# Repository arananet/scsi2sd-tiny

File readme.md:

# SCSI2SD

SCSI2SD is an open project made by Michael McMaster that replace your old SCSI drive device with a SCSI emulator using micro-sd.

# SCSI-TINY

I made this new tiny design from the original SCSI2SD schematics using EAGLE PCB Software. This particular design contains two SD sockets, one for micro-sd and one for SD. This is a working and tested design by many users. They are on sale in AmigaStore and also a batch has been made in 2018 for the RETROWIKI forum.

# Updates

25/10/2019: Initial release. HW made in 2018.

# License

SCSI2SD copyright (c) Michael McMaster | http://www.codesrc.com/mediawiki/index.php?title=SCSI2SD

SCSI2SD-Tiny copyright (c) 2018 Eduardo Arana | @edu_arana

This project is released under the GNU v3 license. You can redistribute it and/or modify it under the terms of the GNU General Public License as published by the Free Software Foundation, either version 3 of the License, or (at your option) any later version.

This program is distributed in the hope that it will be useful, but WITHOUT ANY WARRANTY.

See the GNU General Public License for more details.

There is a copy of the GPLv3 license in this repository. If not, see http://www.gnu.org/licenses/.

## The source/designs of any modifications must be provided to those you distribute the board to.

# Feedback

If you find any error on this description, please drop me an email to info@arananet.net or # Feedback

If you find any error on this description, please drop me an email to info@arananet.net or If you like the project or want to support it, you can buy me a beer or a KO-FI :)

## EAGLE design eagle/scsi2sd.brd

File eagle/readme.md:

If you are gonna produce a batch of this board remember to quote the original authors, don't be a pcb lammer, leave the original authors on the PCB.

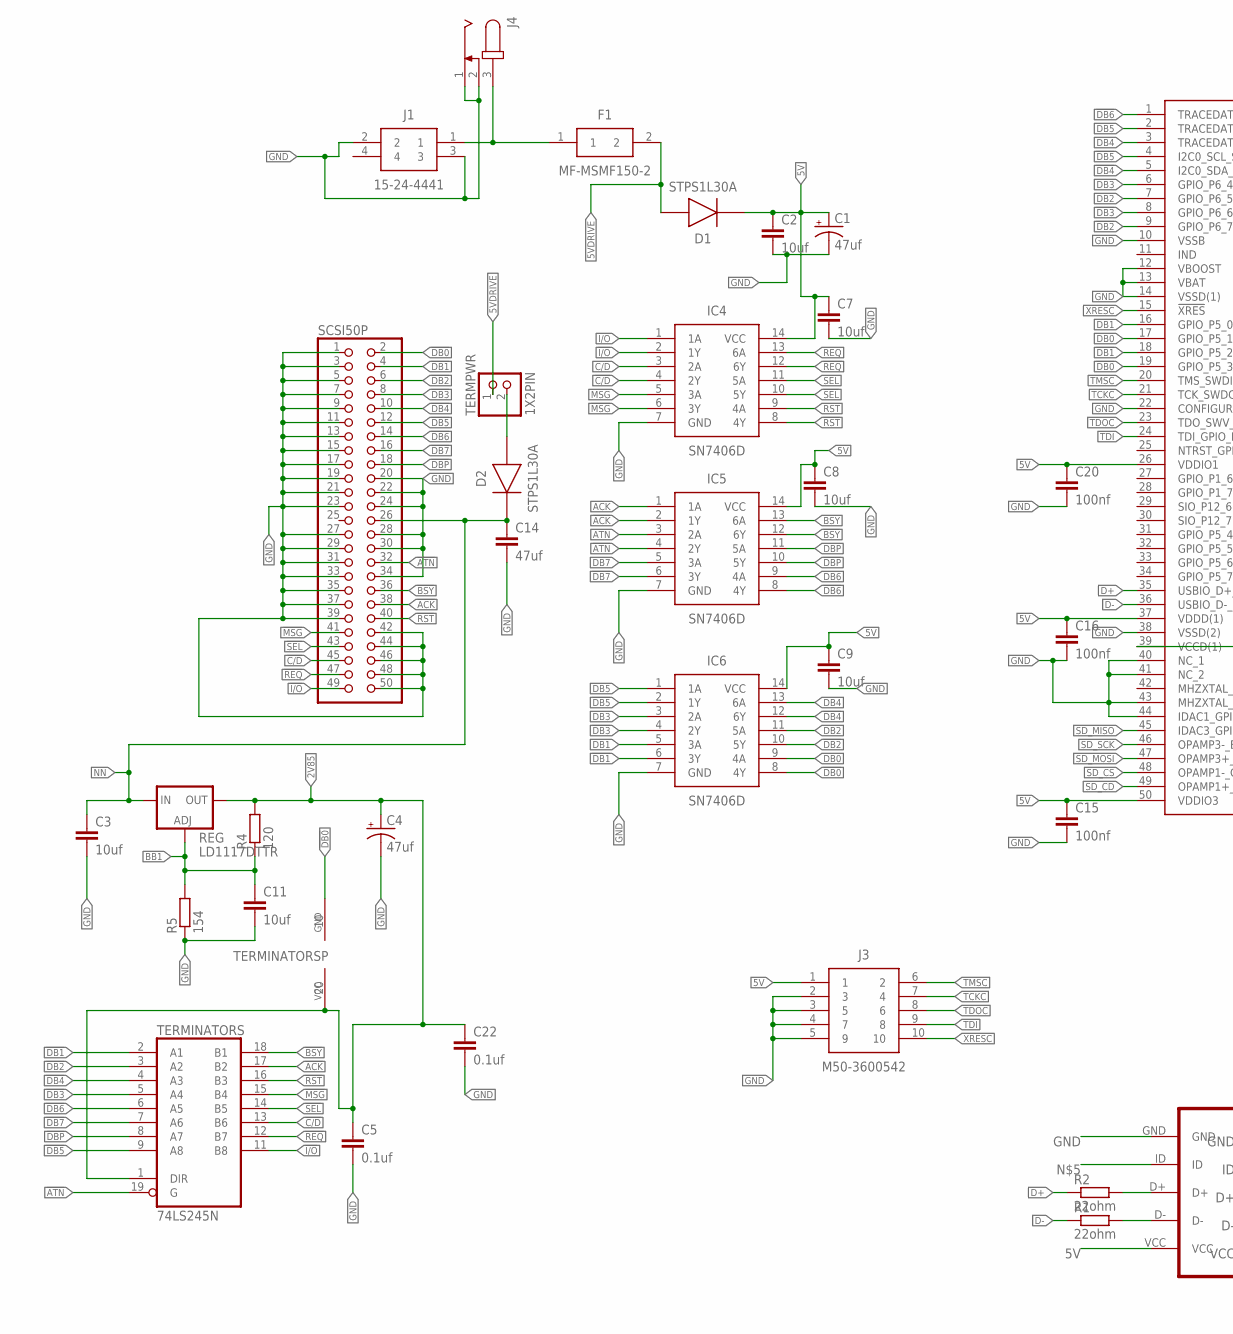
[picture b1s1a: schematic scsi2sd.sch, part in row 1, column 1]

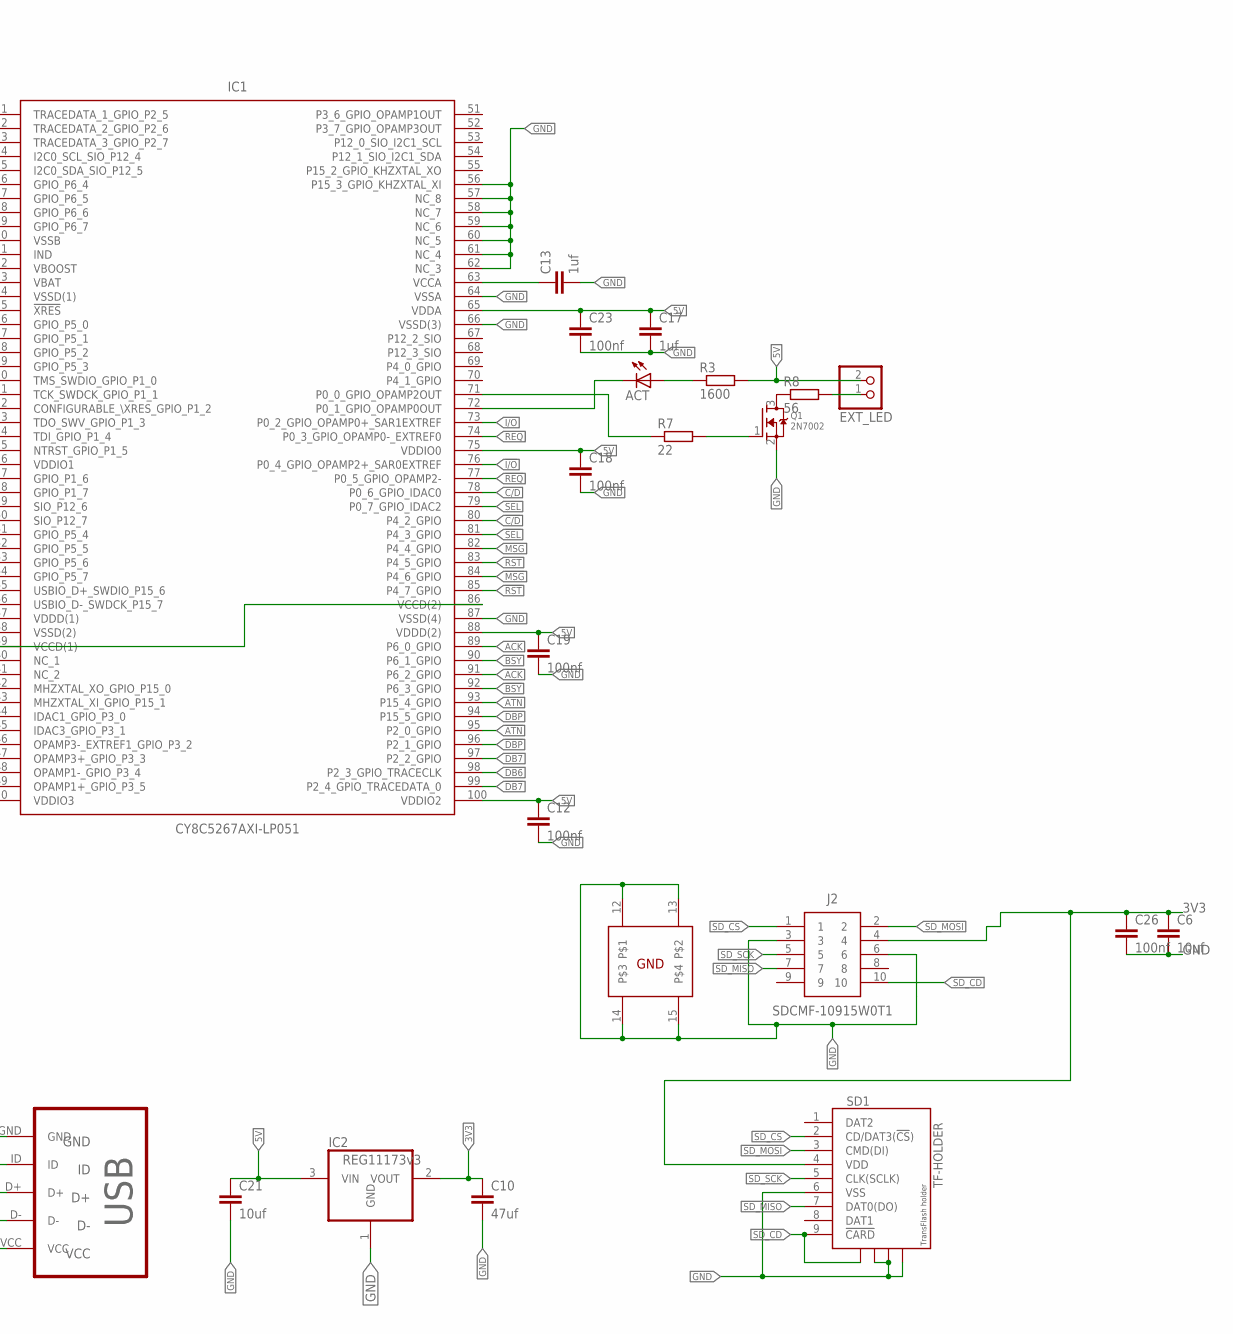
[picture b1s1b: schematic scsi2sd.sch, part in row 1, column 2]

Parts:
ACT: LEDCHIPLED_0805; CHIPLED_0805
C1, C4: 47uf; E2,5-5
C2, C3, C6, C7, C8, C9, C11, C21: 10uf; C0603
C5, C22: 0.1uf; C0603
C10: 47uf; C0603
C12, C15, C16, C18, C19, C20, C23, C26: 100nf; C0603
C13, C17: 1uf; C0603
C14: 47uf; C1206
D1, D2: STPS1L30A; DIOM5226X223N
EXT_LED: 1X2PIN
F1: MF-MSMF150-2; FUSC4632X85N
IC1: CY8C5267AXI-LP051; TQFP50P1600X1600X160-100N
IC2: REG11173v3; SOT223
IC4, IC5, IC6: SN7406D; SOIC127P600X175-14N
J1: 15-24-4441
J2: SDCMF-10915W0T1
J3: M50-3600542; HARWIN_10PIN_1.27PITCH_SMD
J4: RAPC7120; RAPC712
Q1: 2N7002; SOT23
R1, R2: 22ohm; R0603
R3: 1600; R0603
R4: 120; R0603
R5: 154; R0603
R7: 22; R0603
R8: 56; R0603
REG: LD1117DTTR; DPACK
SCSI50P: PINHD-2X25/90; 2X25/90
SD1: TF-HOLDER; TF-PULL
TERMINATORS: 74LS245N; DIL20
TERMPWR: 1X2PIN
USB: MICRO-USB-B; MICRO_USB_4_LEGS

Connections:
2V85: C4.+, C5.1, C22.1, R4.2, REG.4 (OUT), TERMINATORS.1 (DIR), TERMINATORS.20 (VCC)
3V3: C6.1, C10.1, C26.1, IC2.2 (VOUT), J2.4, SD1.4 (VDD)
5V: C1.+, C2.1, C7.1, C8.1, C9.1, C12.1, C15.1, C16.1, C17.1, C18.1, C19.1, C20.1, C21.1, C23.1, D1.1 (K), EXT_LED.2, IC1.26 (VDDIO1), IC1.37 (VDDD(1)), IC1.50 (VDDIO3), IC1.65 (VDDA), IC1.75 (VDDIO0), IC1.88 (VDDD(2)), IC1.100 (VDDIO2), IC2.3 (VIN), IC4.14 (VCC), IC5.14 (VCC), IC6.14 (VCC), J3.1, R3.2, USB.VCC
5VDRIVE: D1.2 (A), F1.2, TERMPWR.1
!ACK: IC1.91 (P6_2_GPIO), IC5.2 (1Y), SCSI50P.38, TERMINATORS.17 (B2)
!ATN: IC1.95 (P2_0_GPIO), IC5.4 (2Y), SCSI50P.32, TERMINATORS.19 (G)
!BSY: IC1.92 (P6_3_GPIO), IC5.12 (6Y), SCSI50P.36, TERMINATORS.18 (B1)
!C/D: IC1.80 (P4_2_GPIO), IC4.4 (2Y), SCSI50P.45, TERMINATORS.13 (B6)
!DB0: IC1.19 (GPIO_P5_3), IC6.8 (4Y), SCSI50P.2, TERMINATORS.10 (GND)
!DB1: IC1.18 (GPIO_P5_2), IC6.6 (3Y), SCSI50P.4, TERMINATORS.2 (A1)
!DB2: IC1.9 (GPIO_P6_7), IC6.10 (5Y), SCSI50P.6, TERMINATORS.3 (A2)
!DB3: IC1.8 (GPIO_P6_6), IC6.4 (2Y), SCSI50P.8, TERMINATORS.5 (A4)
!DB4: IC1.5 (I2C0_SDA_SIO_P12_5), IC6.12 (6Y), SCSI50P.10, TERMINATORS.4 (A3)
!DB5: IC1.4 (I2C0_SCL_SIO_P12_4), IC6.2 (1Y), SCSI50P.12, TERMINATORS.9 (A8)
!DB6: IC1.1 (TRACEDATA_1_GPIO_P2_5), IC5.8 (4Y), SCSI50P.14, TERMINATORS.6 (A5)
!DB7: IC1.99 (P2_4_GPIO_TRACEDATA_0), IC5.6 (3Y), SCSI50P.16, TERMINATORS.7 (A6)
!DBP: IC1.96 (P2_1_GPIO), IC5.10 (5Y), SCSI50P.18, TERMINATORS.8 (A7)
!I/O: IC1.76 (P0_4_GPIO_OPAMP2+_SAR0EXTREF), IC4.2 (1Y), SCSI50P.49, TERMINATORS.11 (B8)
!MSG: IC1.84 (P4_6_GPIO), IC4.6 (3Y), SCSI50P.41, TERMINATORS.15 (B4)
!REQ: IC1.77 (P0_5_GPIO_OPAMP2-), IC4.12 (6Y), SCSI50P.47, TERMINATORS.12 (B7)
!RST: IC1.85 (P4_7_GPIO), IC4.8 (4Y), SCSI50P.40, TERMINATORS.16 (B3)
!SEL: IC1.81 (P4_3_GPIO), IC4.10 (5Y), SCSI50P.43, TERMINATORS.14 (B5)
ACK: IC1.89 (P6_0_GPIO), IC5.1 (1A)
ATN: IC1.93 (P15_4_GPIO), IC5.3 (2A)
BB1: C11.1, R4.1, R5.2, REG.1 (ADJ)
BSY: IC1.90 (P6_1_GPIO), IC5.13 (6A)
C/D: IC1.78 (P0_6_GPIO_IDAC0), IC4.3 (2A)
D+: IC1.35 (USBIO_D+_SWDIO_P15_6), R2.1
D-: IC1.36 (USBIO_D-_SWDCK_P15_7), R1.1
DB0: IC1.17 (GPIO_P5_1), IC6.9 (4A)
DB1: IC1.16 (GPIO_P5_0), IC6.5 (3A)
DB2: IC1.7 (GPIO_P6_5), IC6.11 (5A)
DB3: IC1.6 (GPIO_P6_4), IC6.3 (2A)
DB4: IC1.3 (TRACEDATA_3_GPIO_P2_7), IC6.13 (6A)
DB5: IC1.2 (TRACEDATA_2_GPIO_P2_6), IC6.1 (1A)
DB6: IC1.98 (P2_3_GPIO_TRACECLK), IC5.9 (4A)
DB7: IC1.97 (P2_2_GPIO), IC5.5 (3A)
DBP: IC1.94 (P15_5_GPIO), IC5.11 (5A)
GND: C1.-, C2.2, C3.2, C4.-, C5.2, C6.2, C7.2, C8.2, C9.2, C10.2, C11.2, C12.2, C13.2, C14.2, C15.2, C16.2, C17.2, C18.2, C19.2, C20.2, C21.2, C22.2, C23.2, C26.2, IC1.10 (VSSB), IC1.12 (VBOOST), IC1.13 (VBAT), IC1.14 (VSSD(1)), IC1.22 (CONFIGURABLE_\XRES_GPIO_P1_2), IC1.38 (VSSD(2)), IC1.40 (NC_1), IC1.41 (NC_2), IC1.43 (MHZXTAL_XI_GPIO_P15_1), IC1.44 (IDAC1_GPIO_P3_0), IC1.56 (P15_3_GPIO_KHZXTAL_XI), IC1.57 (NC_8), IC1.58 (NC_7), IC1.59 (NC_6), IC1.60 (NC_5), IC1.61 (NC_4), IC1.62 (NC_3), IC1.64 (VSSA), IC1.66 (VSSD(3)), IC1.87 (VSSD(4)), IC2.1 (GND), IC4.7 (GND), IC5.7 (GND), IC6.7 (GND), J1.2, J1.3, J2.3, J2.6, J2.12, J2.13, J2.14, J2.15, J3.2 (3), J3.3 (5), J3.4 (7), J3.5 (9), J4.1, J4.2, Q1.2 (S), R5.1, SCSI50P.1, SCSI50P.3, SCSI50P.5, SCSI50P.7, SCSI50P.9, SCSI50P.11, SCSI50P.13, SCSI50P.15, SCSI50P.17, SCSI50P.19, SCSI50P.20, SCSI50P.21, SCSI50P.22, SCSI50P.23, SCSI50P.24, SCSI50P.27, SCSI50P.28, SCSI50P.29, SCSI50P.30, SCSI50P.31, SCSI50P.33, SCSI50P.34, SCSI50P.35, SCSI50P.37, SCSI50P.39, SCSI50P.42, SCSI50P.44, SCSI50P.46, SCSI50P.48, SCSI50P.50, SD1.6 (VSS), SD1.S2, SD1.S3, SD1.S4, USB.GND
I/O: IC1.73 (P0_2_GPIO_OPAMP0+_SAR1EXTREF), IC4.1 (1A)
MSG: IC1.82 (P4_4_GPIO), IC4.5 (3A)
unnamed: F1.1, J1.1, J4.3
unnamed: R2.2, USB.D+
unnamed: R1.2, USB.D-
unnamed: ACT.A, R3.1
unnamed: IC1.71 (P0_0_GPIO_OPAMP2OUT), R7.1
unnamed: D2.2 (A), TERMPWR.2
unnamed: IC1.39 (VCCD(1)), IC1.86 (VCCD(2))
unnamed: Q1.1 (G), R7.2
unnamed: Q1.3 (D), R8.1
unnamed: EXT_LED.1, R8.2
unnamed: C13.1, IC1.63 (VCCA)
unnamed: ACT.C, IC1.72 (P0_1_GPIO_OPAMP0OUT)
NN: C3.1, C14.1, D2.1 (K), REG.3 (IN), SCSI50P.26
REQ: IC1.74 (P0_3_GPIO_OPAMP0-_EXTREF0), IC4.13 (6A)
RST: IC1.83 (P4_5_GPIO), IC4.9 (4A)
SD_CD: IC1.49 (OPAMP1+_GPIO_P3_5), J2.10, SD1.9 (!CARD), SD1.S1
SD_CS: IC1.48 (OPAMP1-_GPIO_P3_4), J2.1, SD1.2 (CD/DAT3(!CS!))
SD_MISO: IC1.45 (IDAC3_GPIO_P3_1), J2.7, SD1.7 (DAT0(DO))
SD_MOSI: IC1.47 (OPAMP3+_GPIO_P3_3), J2.2, SD1.3 (CMD(DI))
SD_SCK: IC1.46 (OPAMP3-_EXTREF1_GPIO_P3_2), J2.5, SD1.5 (CLK(SCLK))
SEL: IC1.79 (P0_7_GPIO_IDAC2), IC4.11 (5A)
TCKC: IC1.21 (TCK_SWDCK_GPIO_P1_1), J3.7 (4)
TDI: IC1.24 (TDI_GPIO_P1_4), J3.9 (8)
TDOC: IC1.23 (TDO_SWV_GPIO_P1_3), J3.8 (6)
TMSC: IC1.20 (TMS_SWDIO_GPIO_P1_0), J3.6 (2)
XRESC: IC1.15 (!XRES), J3.10

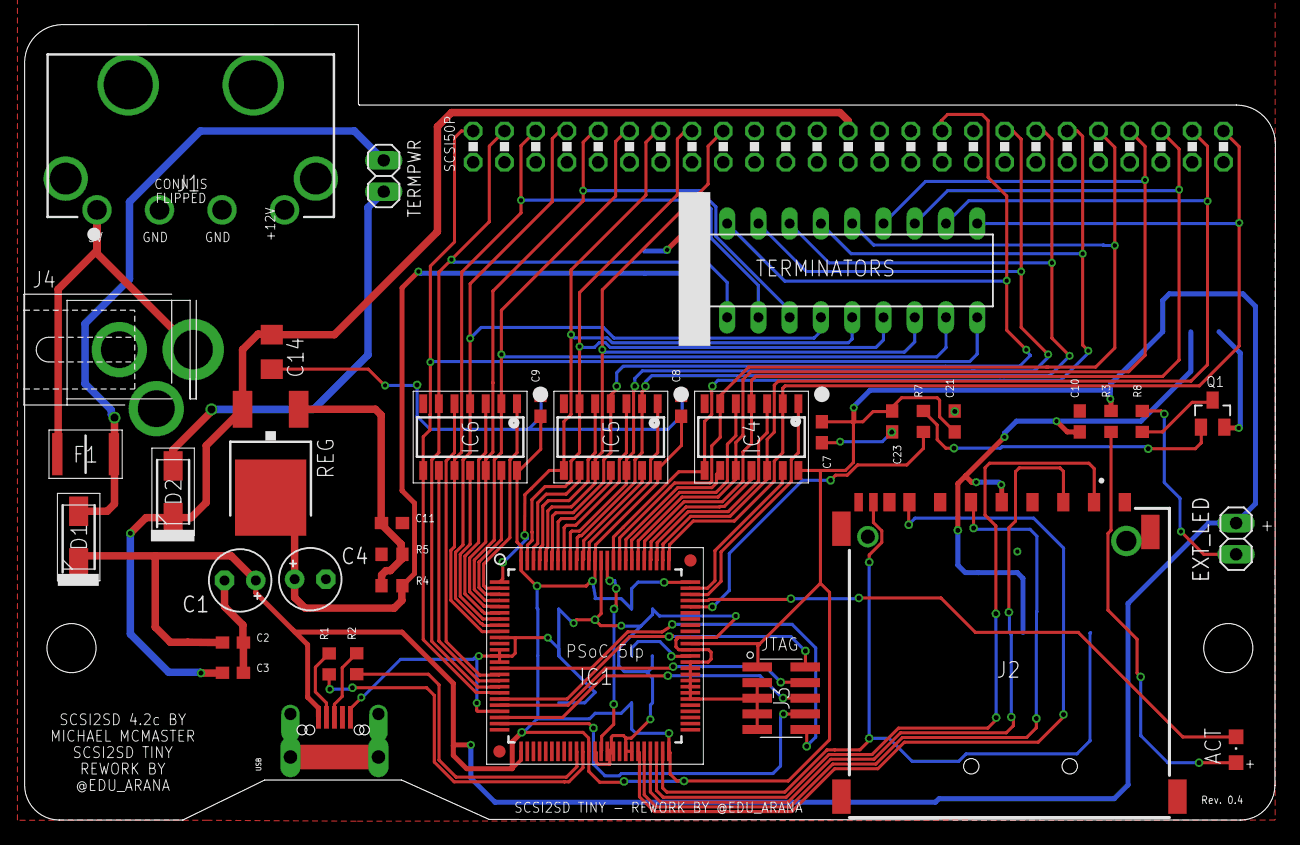
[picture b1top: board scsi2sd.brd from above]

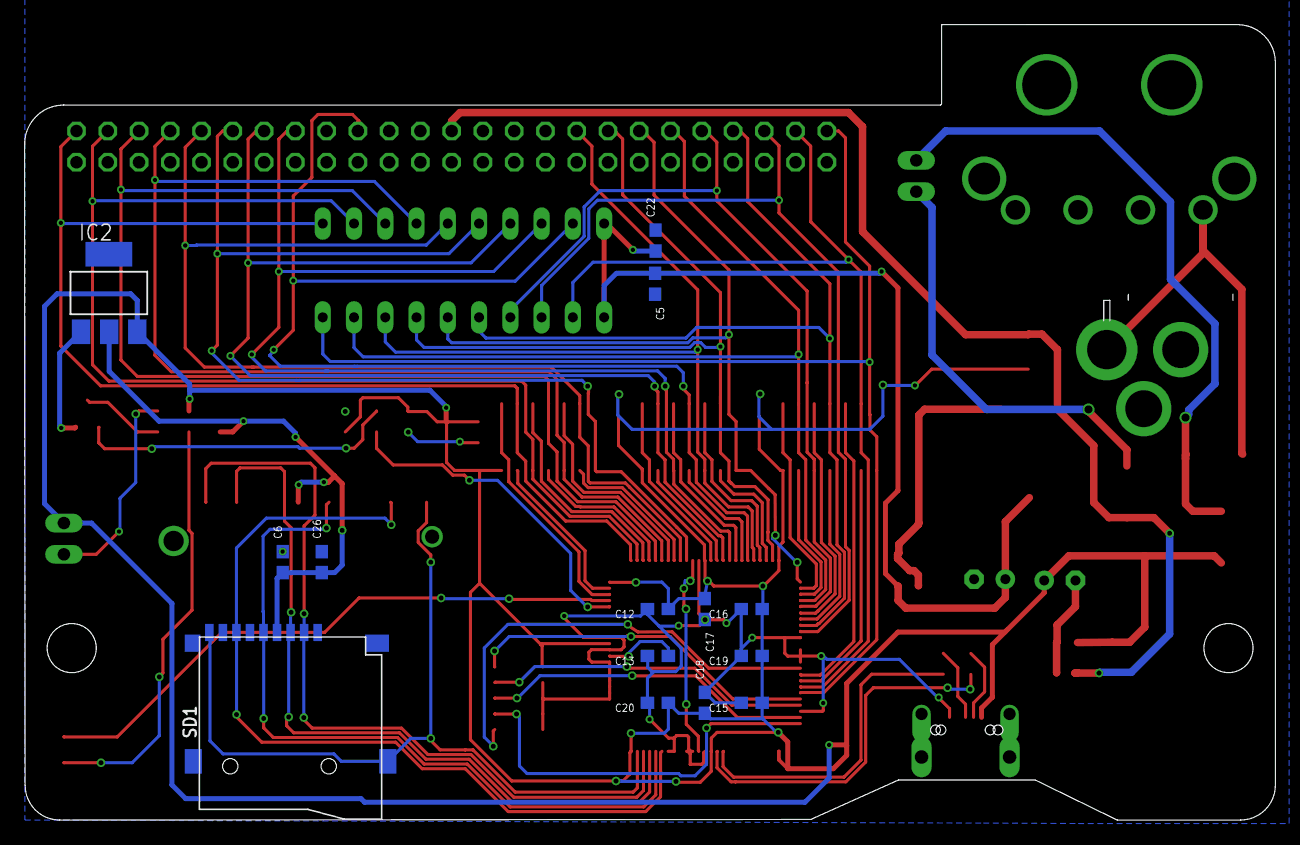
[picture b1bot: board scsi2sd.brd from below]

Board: 2 copper layers, 101.6 x 64.6 mm, 52 parts (14 on the bottom side), 67 nets.

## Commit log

2019-10-28 Create LICENSE
